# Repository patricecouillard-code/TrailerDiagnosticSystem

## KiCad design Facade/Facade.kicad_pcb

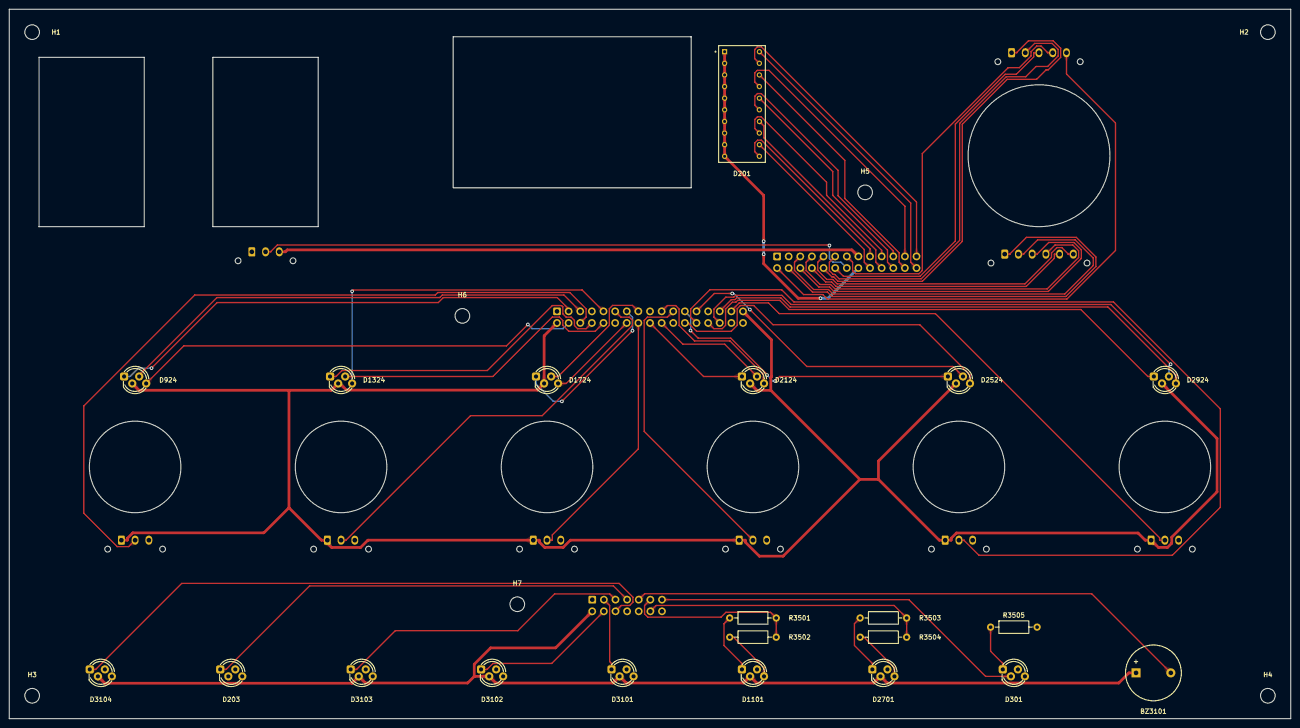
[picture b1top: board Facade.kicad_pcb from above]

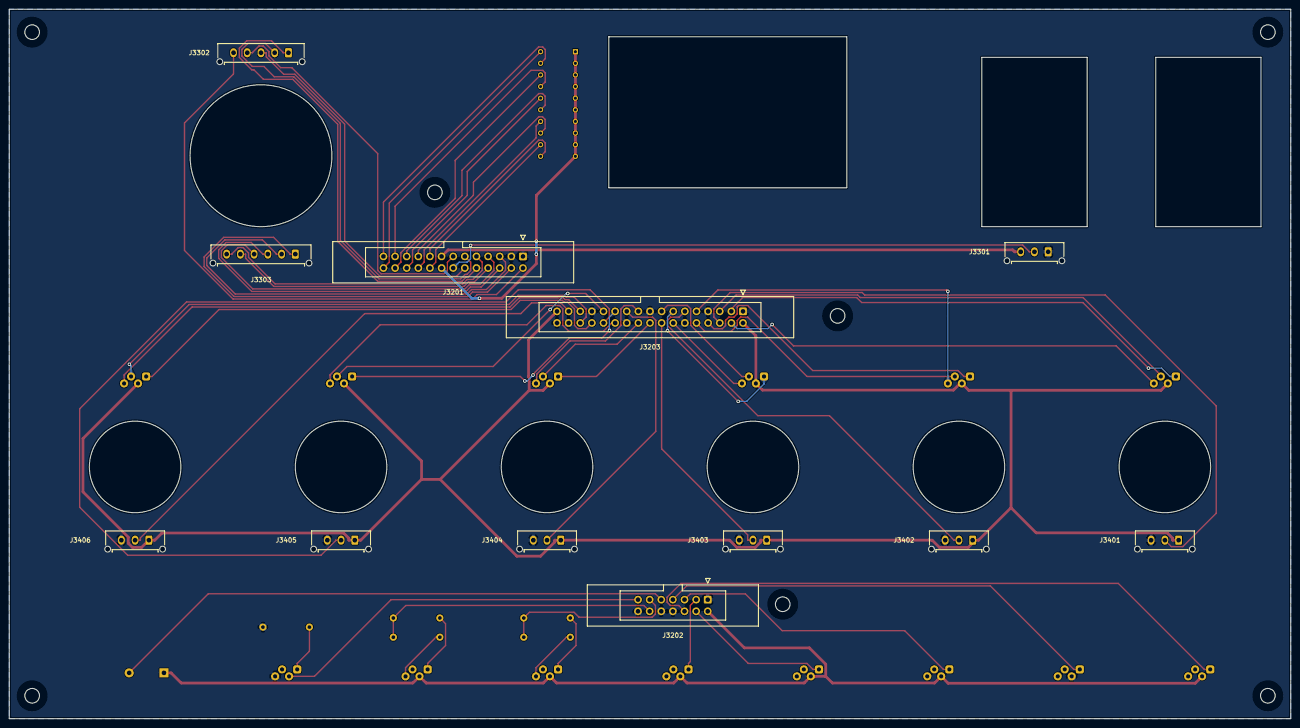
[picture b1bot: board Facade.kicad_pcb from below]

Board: 2 copper layers, 280.0 x 155.0 mm, 40 parts (12 on the bottom side), 65 nets.

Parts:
BZ3101: Buzzer 5V; Buzzer_12x9.5RM7.6
D201: OSX10201-GYR1; DIP760W45P254L2550H815Q20B
D203, D3101, D3102, D3103, D3104: RGB 5mm CA (rouge); LED_D5.0mm-4_RGB_Staggered_Pins
D301, D1101, D2701: RGB 5mm CA (ambre); LED_D5.0mm-4_RGB_Staggered_Pins
D924, D1324, D1724, D2124, D2524, D2924: RGB 5mm CA; LED_D5.0mm-4_RGB_Staggered_Pins
H1, H2, H3, H4, H5, H6, H7: M3; MountingHole_3.2mm_M3
J3201: IDC 2x13; IDC-Header_2x13_P2.54mm_Latch_Vertical
J3202: IDC 2x07; IDC-Header_2x07_P2.54mm_Latch_Vertical
J3203: IDC 2x17; IDC-Header_2x17_P2.54mm_Latch_Vertical
J3301, J3401, J3402, J3403, J3404, J3405, J3406: Micro-Fit 3.0 1x03; Molex_Micro-Fit_3.0_43650-0315_1x03_P3.00mm_Vertical
J3302: Micro-Fit 3.0 1x05; Molex_Micro-Fit_3.0_43650-0515_1x05_P3.00mm_Vertical
J3303: Micro-Fit 3.0 1x06; Molex_Micro-Fit_3.0_43650-0615_1x06_P3.00mm_Vertical
R3501, R3503: 820Ω; R_Axial_DIN0207_L6.3mm_D2.5mm_P10.16mm_Horizontal
R3502, R3504: 1.2kΩ; R_Axial_DIN0207_L6.3mm_D2.5mm_P10.16mm_Horizontal
R3505: 270Ω; R_Axial_DIN0207_L6.3mm_D2.5mm_P10.16mm_Horizontal

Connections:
/Bottom_Zone/Batt_Ext_Rouge: D301.1 (RK), R3505.1
/Bottom_Zone/Facade_Buzzer: BZ3101.2 (-), J3202.9
/Bottom_Zone/Facade_DEL_Batt_Ext: D301.2 (A), J3202.13
/Bottom_Zone/Facade_DEL_Court_Bus: D3102.1 (RK), J3202.4
/Bottom_Zone/Facade_DEL_Incoherence: D3103.1 (RK), J3202.5
/Bottom_Zone/Facade_DEL_Inversion: D203.1 (RK), J3202.7
/Bottom_Zone/Facade_DEL_Masse: D3104.1 (RK), J3202.6
/Bottom_Zone/Facade_DEL_Surchauffe_Aux: J3202.12, R3503.2, R3504.2
/Bottom_Zone/Facade_DEL_Surchauffe_Brake: J3202.11, R3501.2, R3502.2
/Bottom_Zone/Facade_DEL_Surtension: D3101.1 (RK), J3202.3
/Bottom_Zone/Surchauffe_Aux_Rouge: D2701.1 (RK), R3503.1
/Bottom_Zone/Surchauffe_Aux_Vert: D2701.4 (GK), R3504.1
/Bottom_Zone/Surchauffe_Brake_Rouge: D1101.1 (RK), R3501.1
/Bottom_Zone/Surchauffe_Brake_Vert: D1101.4 (GK), R3502.1
/Bottom_Zone/V_Ref: BZ3101.1 (+), D1101.2 (A), D2701.2 (A), D3101.2 (A), D3102.2 (A), D3103.2 (A), D3104.2 (A), J3202.2
/Center_Zone/Facade_Aux_B: D2924.3 (BK), J3203.30
/Center_Zone/Facade_Aux_G: D2924.4 (GK), J3203.29
/Center_Zone/Facade_Aux_R: D2924.1 (RK), J3203.28
/Center_Zone/Facade_Backup_B: D2524.3 (BK), J3203.25
/Center_Zone/Facade_Backup_G: D2524.4 (GK), J3203.24
/Center_Zone/Facade_Backup_R: D2524.1 (RK), J3203.23
/Center_Zone/Facade_Brake_B: D1324.3 (BK), J3203.10
/Center_Zone/Facade_Brake_G: D1324.4 (GK), J3203.9
/Center_Zone/Facade_Brake_R: D1324.1 (RK), J3203.8
/Center_Zone/Facade_Btn_Aux: J3203.31, J3406.2
/Center_Zone/Facade_Btn_Backup: J3203.26, J3405.2
/Center_Zone/Facade_Btn_Brake: J3203.11, J3402.2
/Center_Zone/Facade_Btn_Left: J3203.16, J3403.2
/Center_Zone/Facade_Btn_Right: J3203.21, J3404.2
/Center_Zone/Facade_Btn_Tail: J3203.6, J3401.2
/Center_Zone/Facade_Left_B: D1724.3 (BK), J3203.15
/Center_Zone/Facade_Left_G: D1724.4 (GK), J3203.14
/Center_Zone/Facade_Left_R: D1724.1 (RK), J3203.13
/Center_Zone/Facade_Right_B: D2124.3 (BK), J3203.20
/Center_Zone/Facade_Right_G: D2124.4 (GK), J3203.19
/Center_Zone/Facade_Right_R: D2124.1 (RK), J3203.18
/Center_Zone/Facade_Tail_B: D924.3 (BK), J3203.5
/Center_Zone/Facade_Tail_G: D924.4 (GK), J3203.4
/Center_Zone/Facade_Tail_R: D924.1 (RK), J3203.3
/Center_Zone/V_Ref: D924.2 (A), D1324.2 (A), D1724.2 (A), D2124.2 (A), D2524.2 (A), D2924.2 (A), J3203.2, J3203.33, J3401.1, J3402.1, J3403.1, J3404.1, J3405.1, J3406.1
/Top_Zone/Facade_Jauge_1: D201.11, J3201.17
/Top_Zone/Facade_Jauge_2: D201.12, J3201.18
/Top_Zone/Facade_Jauge_3: D201.13, J3201.19
/Top_Zone/Facade_Jauge_4: D201.14, J3201.20
/Top_Zone/Facade_Jauge_5: D201.15, J3201.21
/Top_Zone/Facade_Jauge_6: D201.16, J3201.22
/Top_Zone/Facade_Jauge_7: D201.17, J3201.23
/Top_Zone/Facade_Jauge_8: D201.18, J3201.24
/Top_Zone/Facade_Jauge_9: D201.19, J3201.25
/Top_Zone/Facade_Jauge_10: D201.20, J3201.26
/Top_Zone/Facade_VLed_Jauge: D201.1, D201.2, D201.3, D201.4, D201.5, D201.6, D201.7, D201.8, D201.9, D201.10, J3201.16
/Top_Zone/Facade_VM_Mesure: J3201.2, J3302.5
/Top_Zone/Facade_VM_Sel_Batt: J3201.4, J3303.1
/Top_Zone/Facade_VM_Sel_Trailer_Aux: J3201.12, J3302.3
/Top_Zone/Facade_VM_Sel_Trailer_Pince: J3201.13, J3302.4
/Top_Zone/Facade_VM_Sel_Vehic_Aux: J3201.10, J3302.1
/Top_Zone/Facade_VM_Sel_Vehic_Backup: J3201.9, J3303.6
/Top_Zone/Facade_VM_Sel_Vehic_Brake: J3201.6, J3303.3
/Top_Zone/Facade_VM_Sel_Vehic_Left: J3201.7, J3303.4
/Top_Zone/Facade_VM_Sel_Vehic_Pince: J3201.11, J3302.2
/Top_Zone/Facade_VM_Sel_Vehic_Right: J3201.8, J3303.5
/Top_Zone/Facade_VM_Sel_Vehic_Tail: J3201.5, J3303.2
/Top_Zone/Mode_Trailer: J3201.14, J3301.2
/Top_Zone/V_Ref: J3201.15, J3301.3
GND: D203.2 (A), D301.4 (GK), J3201.1, J3201.3, J3202.1, J3202.8, J3202.10, J3202.14, J3203.1, J3203.7, J3203.12, J3203.17, J3203.22, J3203.27, J3203.32, J3203.34, J3301.1, J3401.3, J3402.3, J3403.3, J3404.3, J3405.3, J3406.3, R3505.2
